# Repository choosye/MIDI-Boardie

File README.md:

# MIDI-Boardie
Half Life Hack Club Week 3 - MIDI Keypad

A custom MIDI Keypad to play around with music and have fun! Learning PCB design while making music come to life :D 

## Why? 
This project was created as part of Hack Club's Half Life Week 3 beginner tutorial to hone skills in PCB design. 
I wanted to learn more about PCB design by creating something interactive and music-related. This project is also an opportunity for me to explore how electronic components work together to create a functional MIDI controller!

## Project Status
The KiCad schematic and PCB layout have been designed, with slight customisations to make the keypad my own. The next steps are to manufacture the PCB and develop the firmware. 
The firmware will use KMK, a Python-based keyboard firmware framework. The project has not yet been tested on physical hardware, and further customisation and testing will happen as I continue learning :)
Schematic: 
PCB Layout: 

## Software & Tools
- KiCad - Schematic and PCB design
- KMK - Firmware for the MIDI Keyboard

## Repository Contents
- [PCB/](PCB/) - KiCad Schematic and PCB Design Files
- [Firmware/](Firmware/) - KMK Firmware files

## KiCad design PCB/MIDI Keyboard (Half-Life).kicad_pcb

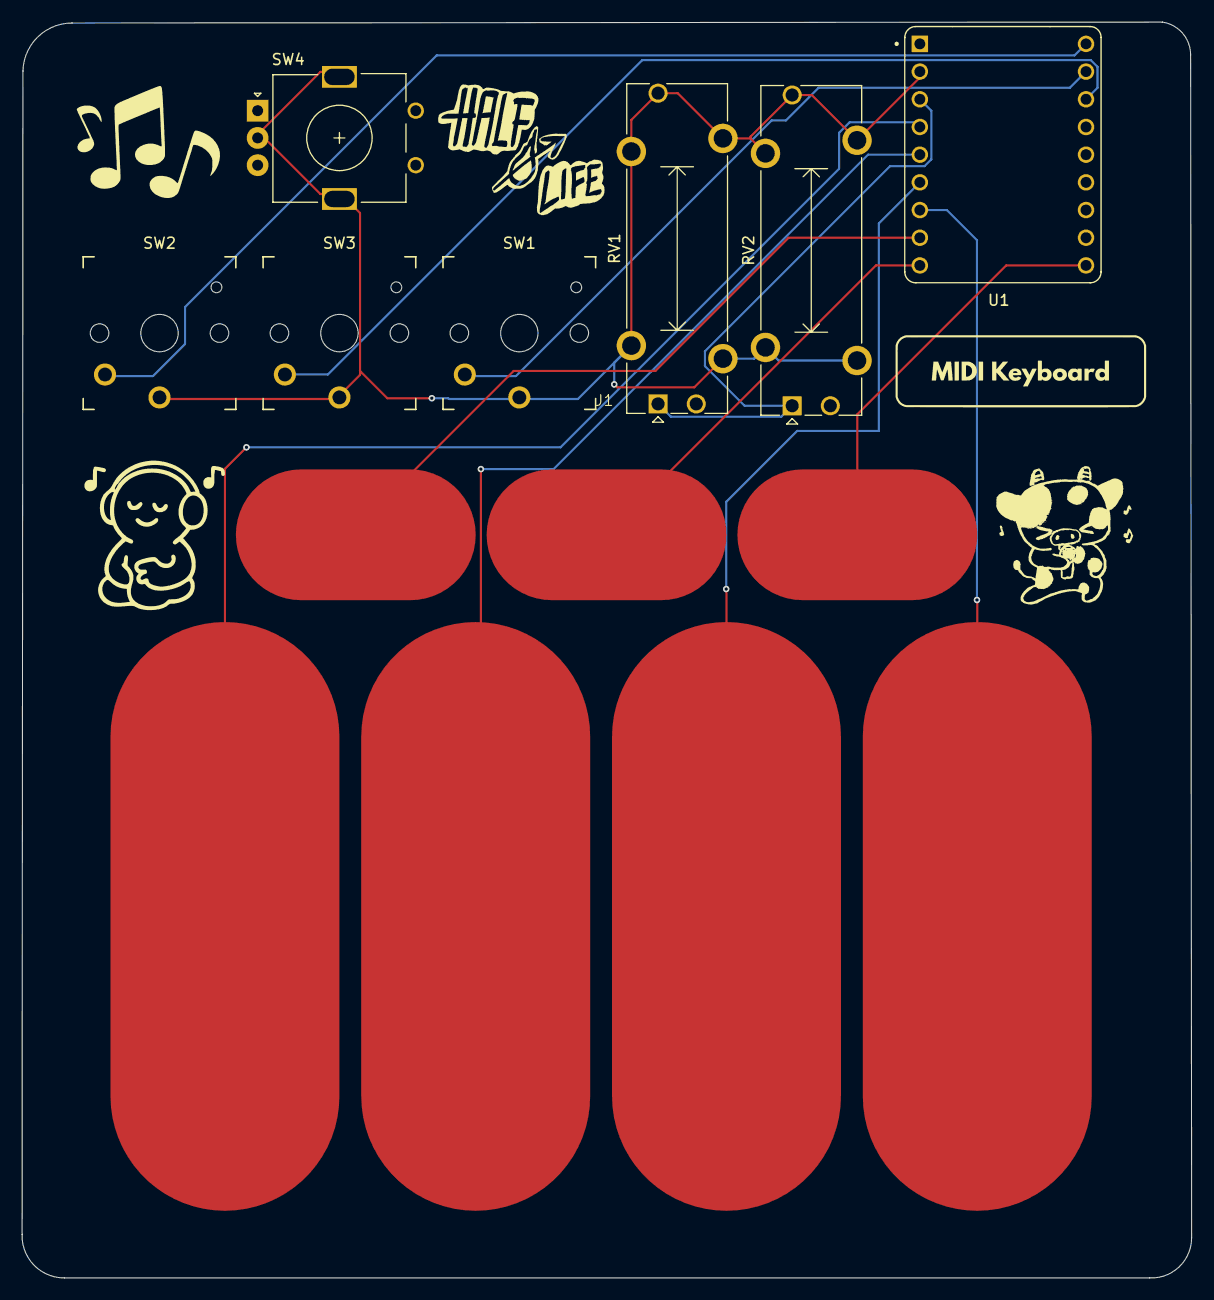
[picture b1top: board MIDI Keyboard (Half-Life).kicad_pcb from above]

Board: 2 copper layers, 107.3 x 115.2 mm, 8 parts (0 on the bottom side), 12 nets.

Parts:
J1: Touch Buttons; Capactive_Keys_Half_Life_Midi
RV1, RV2: Slider; Potentiometer_Bourns_PTA1543_Single_Slide
SW1, SW2, SW3: SW_Push; Kailh Choc Low-Profile Switches
SW4: RotaryEncoder_Switch_MP; RotaryEncoder_Alps_EC11E_Vertical_H20mm
U1: Waveshare ESP32-S3-ZERO; Waveshare ESP32-S3-Zero

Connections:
+3V3: RV1.1, RV2.1, U1.3V3 (3V3(OUT))
/SWITCH1: SW1.2, U1.RX
/SWITCH2: SW2.2, U1.TX
/SWITCH3: SW3.2, U1.13 (GP13)
/TOUCH1: J1.1, U1.1 (GP1)
/TOUCH2: J1.2, U1.2 (GP2)
/TOUCH3: J1.3, U1.3 (GP3)
/TOUCH4: J1.4, U1.4 (GP4)
/TOUCH5: J1.5, U1.5 (GP5)
/TOUCH6: J1.6, U1.6 (GP6)
/TOUCH7: J1.7, U1.7 (GP7)
GND: RV1.3, RV1.MP (MountPin), RV2.3, RV2.MP (MountPin), SW1.1, SW2.1, SW3.1, SW4.C, SW4.MP, U1.GND
